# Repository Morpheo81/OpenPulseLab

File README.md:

# OpenPulseLab
A Low-Cost, Open-Source ECG Monitor for educational and research uses

> [!NOTE]
> This project is currently under active development and is a work in progress (WIP).

---

### A Note on Project Purpose and Responsibility

**This device is an educational and research prototype. It is NOT a certified medical device and should NEVER be used for diagnostic purposes.**

The primary goal of this project is to create an accessible, affordable, and open-source platform for learning about biometrics, signal processing, and IoT. Its simplicity is a feature, designed to lower the barrier to entry for students, hobbyists, and developers in emerging economies. The data quality is intentionally limited in this version, but can be improved with advanced software. By using this project, you acknowledge and agree to the full disclaimer below.

---

## ⚠️ Legal Disclaimer ⚠️

This project is provided "as is," without any warranty of any kind, either express or implied, including, but not limited to, the implied warranties of merchantability, fitness for a particular purpose, or non-infringement. In no event shall the authors or copyright holders be liable for any claim, damages, or other liability, whether in an action of contract, tort, or otherwise, arising from, out of, or in connection with the software, hardware, or the use or other dealings in the project.

**Do not use this device for medical diagnosis, treatment, or any clinical application. Consult a certified medical professional for any health-related concerns.**

---

### About the Project

This project leverages an **ESP8266 microcontroller** to create a simple, Wi-Fi enabled ECG monitor. It processes the analog signals from an **AD8232 ECG sensor module** and serves a web page via an on-board web server. Users can access this page from any web browser to view real-time heart data and save it. The device also includes hardware for **lead-off detection** and a **buzzer/LED** for error signaling.

* **Open and Accessible:** All hardware schematics, firmware, and documentation are provided.
* **Low-Cost:** Built with readily available and inexpensive components.
* **Self-Contained:** Designed to run on a battery, ensuring full electrical isolation and safety from the mains power supply.

### How It Works

1.  **Signal Acquisition:** The AD8232 sensor module captures the electrical signals of the heart.
2.  **Signal Conversion:** The ESP8266's analog-to-digital converter (ADC) reads the output from the AD8232.
3.  **Data Transmission:** The ESP8266 acts as a web server, broadcasting the raw data via Wi-Fi and using **WebSockets** for real-time streaming.
4.  **Data Visualization:** A simple HTML/JavaScript front-end displays the data on a graph in a web browser. A software filter (median on X, moving average on Y) is applied to smooth the raw data.

**Here an example of the Web Server running on ESP8266**

### Potential Applications

While not a medical tool, this project has several fascinating applications:

* **Educational:** A practical, hands-on tool for teaching electronics, programming, and biometrics.
* **Research:** A base platform for research into advanced signal processing algorithms (e.g., using AI to identify patterns in nerve impulses).
* **Human-Computer Interface (HCI):** The same principles can be used to detect neuromuscular signals, allowing the device to act as a controller for a PC or other machines.

### Getting Started

To build your prototipe device, you will need:

* **Components: for Rev 1.0**
    * Buzzer (BZ1) - not mandatory
    * 0.1uF capacitors (C1, C3)
    * 100uF capacitor (C2)
    * capacitor (C5)
    * diodes (D1, D2)
    * PinSocket 1x06 (J2, J3) and 1x02 (J1) connectors
    * Molex 1x02 connector (J4)
    * LED for error (LED1)
    * LED for power (LED2)
    * 10K resistors (R1, R6)
    * 1K resistor (R2)
    * 22K resistors (R3, R4, R5)
    * 100 resistors (R8, R9, R10)
    * SW_Push button (SW1)
    * SW_DIP_x01 switch (SW2)
    * test points (TP1, TP2, TP3, TP4)
    * ESP-12F WiFi module (U1)
 NOTE: SMD resistor and ceramic capacitor are 0805
* **Tools:**
    * Soldering iron and soldering materials.
    * **AD8232 module with electrode.**
    * Serial programmer.

* **Firmware & Libraries:**
    * `ECG_ESP8266.ino` firmware file example for the ECG - main topic
    * `ECG_muscle_ESP8266.ino` firmware file example for use this platform to detect the activation of muscles
    * Arduino Libraries: `ESP8266WiFi`, `ESP8266WebServer`, `WebSocketsServer` by Markus Sattler, `ArduinoJson`
* **Files:**
    * The hardware files are in the `KiCad` folder.
    * The firmware files are in the `ArduinoIDE` folder.
    * The proto of the box is in the `FreeCAD` folder.

### Example of Electrode Placement and Important Notes

This device uses TENS/EMS (Transcutaneous Electrical Nerve Stimulation / Electrical Muscle Stimulation) electrodes instead of traditional, single-use ECG electrodes. While standard ECG electrodes are specifically designed for low impedance and optimal signal fidelity, they are often expensive and intended for single use due to their hydrogel-based adhesive.

Our choice to use TENS/EMS pads is a deliberate design decision to prioritize reusability and user convenience. These pads, commonly used for muscle stimulation, have a more durable adhesive, allowing for multiple uses before replacement. This makes the OpenPulseLab device more cost-effective and accessible, particularly for educational and hobbyist purposes.

It's important to note the technical trade-off involved. The impedance of TENS/EMS pads is typically higher than that of medical-grade ECG electrodes. This can result in a weaker signal from the AD8232 sensor. If you choose to use different types of electrodes, such as standard ECG electrodes, you may need to re-evaluate and adjust the amplification factors and any filtering thresholds within the firmware to achieve the best possible signal quality.

### Licensing

This project is released under the **Creative Commons Attribution-ShareAlike 4.0 International (CC BY-SA 4.0)** license. This means you are free to share and adapt the material for any purpose, even commercially, as long as you provide appropriate attribution and distribute your contributions under the same license.

**Copyright (c) 2025 Fabio Besuzzi**

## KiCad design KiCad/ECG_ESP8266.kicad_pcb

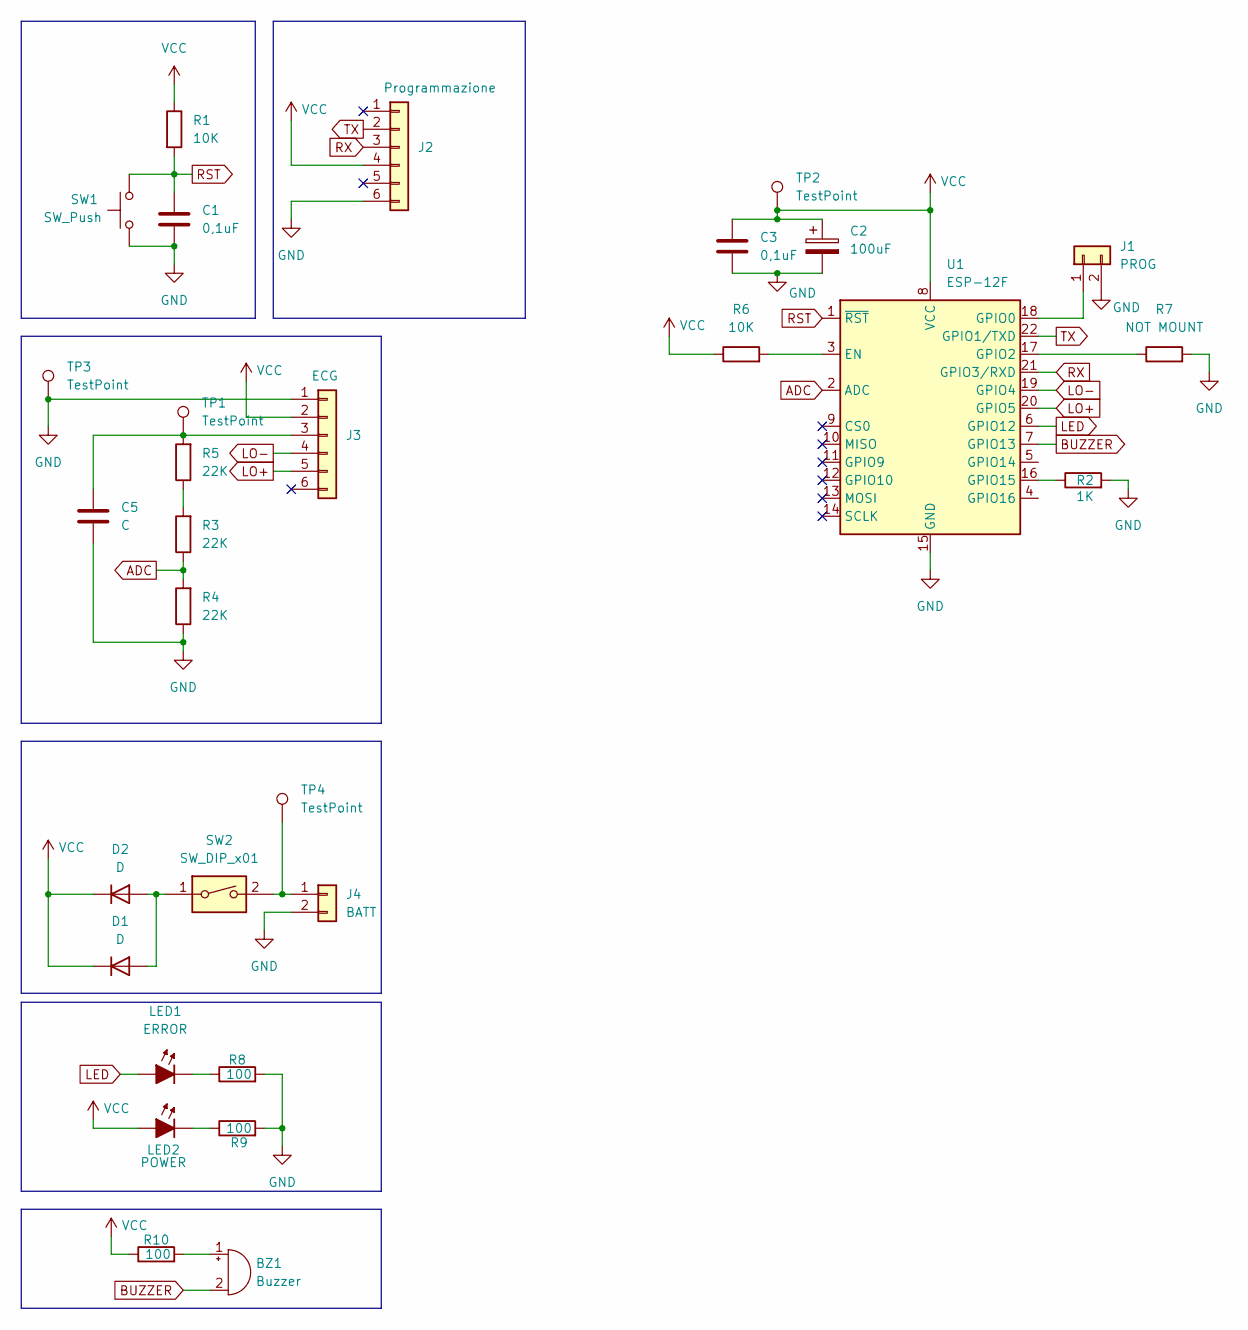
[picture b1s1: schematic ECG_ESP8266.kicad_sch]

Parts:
BZ1: Buzzer; Buzzer_15x7.5RM7.6
C1, C3: 0,1uF; C_0805_2012Metric
C2: 100uF; CP_Elec_5x5.3
C5: C; C_0805_2012Metric
D1: D; D_DO-15_P12.70mm_Horizontal
D2: D; D_0805_2012Metric
J1: PROG; PinSocket_1x02_P2.54mm_Vertical
J2: Programmazione; PinSocket_1x06_P2.54mm_Vertical
J3: ECG; PinSocket_1x06_P2.54mm_Vertical
J4: BATT; Molex_KK-254_AE-6410-02A_1x02_P2.54mm_Vertical
LED1: ERROR; LED_D3.0mm
LED2: POWER; LED_D3.0mm
R1, R6: 10K; R_0805_2012Metric
R2: 1K; R_0805_2012Metric
R3, R4, R5: 22K; R_0805_2012Metric
R7: NOT MOUNT; R_0805_2012Metric
R8, R9, R10: 100; R_0805_2012Metric
SW1: SW_Push; SW_Push_1P1T_NO_6x6mm_H9.5mm
SW2: SW_DIP_x01; PinSocket_1x03_P2.54mm_Vertical
TP1, TP2, TP3, TP4: TestPoint; TestPoint_Loop_D2.54mm_Drill1.5mm_Beaded
U1: ESP-12F; ESP-12E

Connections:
ADC: R3.1, R4.2, U1.2 (ADC)
BUZZER: BZ1.2 (-), U1.7 (GPIO13)
GND: C1.2, C2.2, C3.2, C5.2, J1.2, J2.6, J3.1, J4.2, R2.2, R4.1, R7.2, R8.2, R9.2, SW1.1, TP3.1, U1.15 (GND)
LED: LED1.2 (A), U1.6 (GPIO12)
LO+: J3.5, U1.20 (GPIO5)
LO-: J3.4, U1.19 (GPIO4)
unnamed: BZ1.1 (+), R10.2
unnamed: D1.2 (A), D2.2 (A), SW2.1
unnamed: J1.1, U1.18 (GPIO0)
unnamed: C5.1, J3.3, R5.2, TP1.1
unnamed: J4.1, SW2.2, TP4.1
unnamed: LED1.1 (K), R8.1
unnamed: LED2.1 (K), R9.1
unnamed: R3.2, R5.1
unnamed: R6.2, U1.3 (EN)
unnamed: R7.1, U1.17 (GPIO2)
unnamed: R2.1, U1.16 (GPIO15)
RST: C1.1, R1.2, SW1.2, U1.1 (~RST)
RX: J2.3, U1.21 (GPIO3/RXD)
TX: J2.2, U1.22 (GPIO1/TXD)
VCC: C2.1, C3.1, D1.1 (K), D2.1 (K), J2.4, J3.2, LED2.2 (A), R1.1, R6.1, R10.1, TP2.1, U1.8 (VCC)

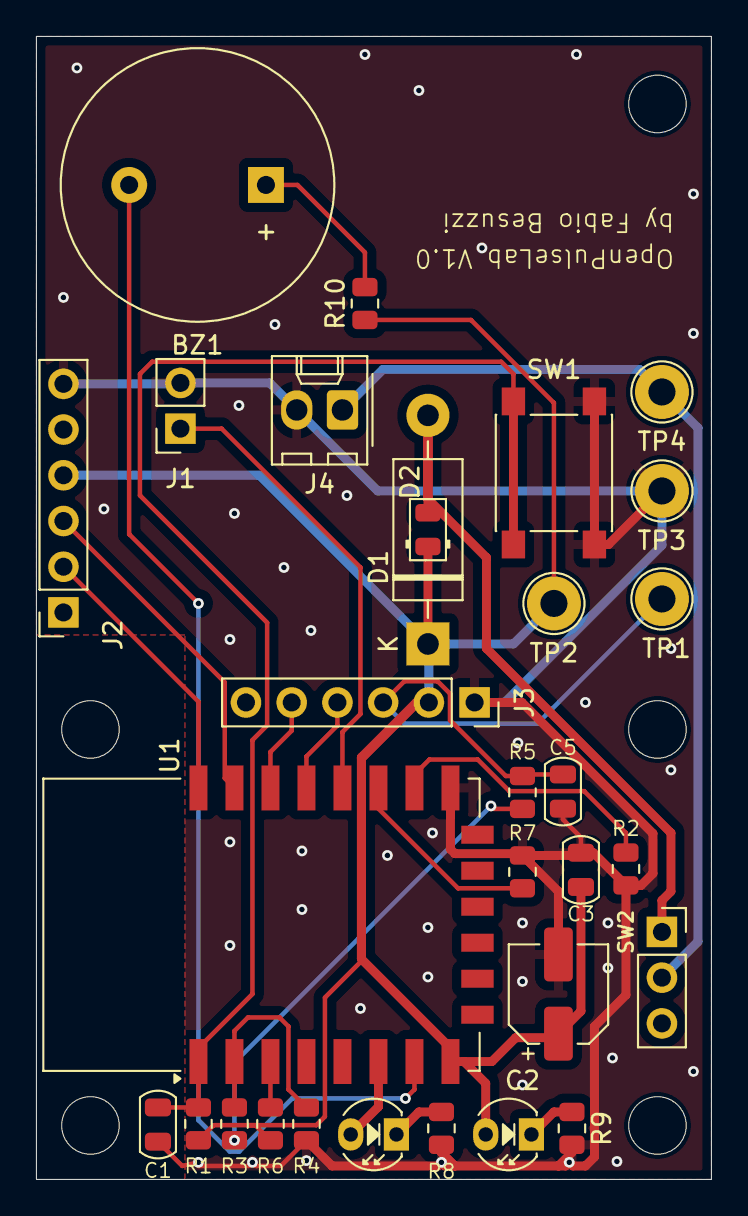
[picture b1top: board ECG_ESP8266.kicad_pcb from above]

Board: 2 copper layers, 37.5 x 63.5 mm, 30 parts (0 on the bottom side), 21 nets.

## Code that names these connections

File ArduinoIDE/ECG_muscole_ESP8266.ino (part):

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WebSocketsServer webSocket = WebSocketsServer(81); // Server WebSockets sulla porta 81

// --- Configurazione Pin Lead-Off Detection (AD8232) ---
// Collega LO+ del AD8232 a D2 (GPIO4) e LO- a D1 (GPIO5) sul tuo NodeMCU/Wemos.
// Verifica la tua board per i pin GPIO effettivi associati a D1, D2, ecc.
// L'AD8232 invia HIGH quando il lead è scollegato, LOW quando è connesso.
// Se il tuo modulo ha logica invertita, potresti dover invertire i 0/1 nel JS.
const int LO_PLUS_PIN = 4;  // Esempio: pin D2 (GPIO4) collegato a LO+ del AD8232
const int LO_MINUS_PIN = 5; // Esempio: pin D1 (GPIO5) collegato a LO- del AD8232

// Pin del LED aggiuntivo da utilizzare per segnalazioni di errori o stato di funzionamento (GPIO12)
const int LED_PIN = 12;

// Pin del BUZZER da utilizzare per allarmi (GPIO13)
const int BUZZER_PIN = 13;


// --- Pagina HTML da servire al Browser ---
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  pinMode(LO_PLUS_PIN, INPUT);
  pinMode(LO_MINUS_PIN, INPUT);

  //Configurazione dei pin del LED e del BUZZER 
  pinMode(LED_PIN, OUTPUT);
  pinMode(BUZZER_PIN, OUTPUT);
  //Impostazione del valore di default: il LED è attivo alto mentre il BUZZER è attivo basso
  digitalWrite(LED_PIN, LOW);
  digitalWrite(BUZZER_PIN, HIGH);


  // Configura l'ESP come Access Point Wi-Fi
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  for(c1=0;c1<5;c1++)
  {
    ecgValue = analogRead(A0);
    digitalWrite(BUZZER_PIN, HIGH);
    if(ecgValue>760){
      digitalWrite(BUZZER_PIN, LOW);
      digitalWrite(LED_PIN, HIGH);
    }
    for(c2=0;c2<5-1;c2++)
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  for(c1=0;c1<9;c1++)
  {
    ecgValue = analogRead(A0);
    digitalWrite(BUZZER_PIN, HIGH);
    delay(1);
    if(ecgValue>760){
      digitalWrite(BUZZER_PIN, LOW);
      digitalWrite(LED_PIN, HIGH);
    }
    for(c2=0;c2<9-1;c2++)
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
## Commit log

2025-09-06 Update README.md
    Prima versione
2025-09-06 Update README.md
    Sistemato link ad immagine
2025-09-06 Update LICENSE
    Aggiornamento licenza secondo suggerimenti di Gemini
2025-09-06 KiCad project for the ESP8266 board
2025-09-06 Example of ESP8266 Web Server for Arduino IDE
2025-09-06 FW example
2025-09-06 Create KiCad
2025-09-06 KiCad Project
2025-09-06 KiCad schematic
2025-09-06 KiCad Board
2025-09-06 Web Server running
2025-09-06 Programming Proto 1.0
2025-09-06 Proto Board 1.0
2025-09-13 Electrodes position
2025-09-13 Update README.md
    Electrodes position example
2025-09-13 New FW with Buzzer and LED
2025-09-14 Update README.md
    Note on TENS/EMS electrode
2025-09-14 Update ECG_ESP8266.ino
    Median on 9 read of ecg signal
2025-09-28 Update ECG_ESP8266.ino
    Added a new graph with a signle pulse calulated as mean.
2025-10-12 FreeCAD prototype project
2025-10-12 Example of FW for muscle activation detection
    Only an example...
2025-10-12 Update README.md
    Some changes after adding FreeCAD files and an example on how to use this devices to control muscles activations.
